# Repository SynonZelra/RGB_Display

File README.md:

RGB Display
===========	
During my work term at Lumotune I worked with developed LCD drivers and wanted to try a completely different type of display that I would be able to make on my own so I looked into making a RGB display. Just like the LED cube, multiplexing and persistence of vision were key techniques required. I used PWM drivers (TLC5940) to drive the specific values to the RGB LEDs in each column and shift registers (CD4094B) to switch between the rows. 
This is the first personal project dealing with complex IC so an online tutorial and base TLC5940 code from Kevin Darrah was used and expanded on: https://www.youtube.com/watch?v=FehBLNHMlfo 

This code was used instead of existing libraries to understand lower level programming and in depth use of TLC5940.
	
Updates:
--------
-	Original design was for 32 columns. This was reduced to 16 columns due to lack of RGB LEDs. The other sections have been updated to take this change into account.

Here is an image of the 16x16 RGB Display:  

Click below for a video of the display:  
<a href="https://youtu.be/2PrOFA3ZqBM">https://youtu.be/2PrOFA3ZqBM</a>

Materials:
----------
(Material list has been updated)
-	x256, 5mm RGB LED
    -	Common anode for PWM driver to sink current, see Figure 1
-	x3, PWM driver [TLC5940](http://www.ti.com/lit/ds/symlink/tlc5940.pdf)
    -	16 channels per chip
    -	12-bit PWM resolution
    -	6-bit dot correction resolution
    -	Current sink
    -	Daisy-chained
-	x2, shift register [CD4094B](http://www.ti.com/lit/ds/symlink/cd4094b.pdf)
    -	8 outputs per chip
    -	Daisy-chained
-	x16, p-channel MOSFET [ZVP4424A](http://www.diodes.com/datasheets/ZVP4424A.pdf) 
-	x5, 0.1uF ceramic capacitor, package 0805
-	x5, 1uF ceramic capacitor, package 0805
-	x2, 10uF tantalum capacitor
-	x1, 5V LDO regulator [LT1096CT](http://cds.linear.com/docs/en/datasheet/1086ffs.pdf)
-	x2, 1x6 female connector header
-	x1, 2.1mm power connector jack
-	x3, 28 position IC socket 
-	Soldering assembly (solder, iron, braid, etc.)
-	Breadboard and jumper wires

Design:
-------
-	LEDs were arranged in an array of 16x16 (256 LEDs, 48 pins per row) addressed by 3 PWM drivers (48 channels) and 2 shift registers (16 outputs)
-	Column data input to PWM drivers through SPI protocol, lighting an entire row at once and row is switched with shift register and new RGB data is sent through PWM driver
-	Shift register cant source enough current to light 16 LEDs so a p-channel MOSFET is used as a high side switch at each row to source required current
-	Base code from Kevin Darrah included:
    -	8-bit to 12-bit conversion for GS data transmission
    -	SPI protocol and timer interrupt setup 
-	Code was expanded on to include:
    -	Brightness and colour correction
    -	8-bit data resolution for easier storage and processing
    -	Shift register, data buffer and multiplexing
-	Schematic capture and PCB layout designed with CadSoft EAGLE

Figure 1: Common Anode RGB LED

Assembly:
---------
Prototype and assembly of RGB display can be seen from the images and videos below:  
  
Figure 2: Testing TLC5940 

Figure 3: 0000104_135116, Testing 2 row multiplexing with TLC5940 and CD4094B  

<a href="https://youtu.be/0XYK6YoSBJY">https://youtu.be/0XYK6YoSBJY</a>  
Video 1: TLCCycle2, Video of cycling through all the colours with TLC5940

<a href="https://youtu.be/0XYK6YoSBJY">https://youtu.be/0XYK6YoSBJY</a>  
Video 2: TLCShift, Video of shifting colours with TLC5940

Figure 4: PCB from SeeedStudio

Figure 5: Soldering the PCB

Figure 6: Testing and debugging the board (malfunctioning MOSFET) while soldering 

Figure 7: 16x16 RGB LED soldered!

Future:
-------
-	Update software to use TLC5940 and TLC5940Mux libraries
-	Import images with Python through serial port and show on RGB display

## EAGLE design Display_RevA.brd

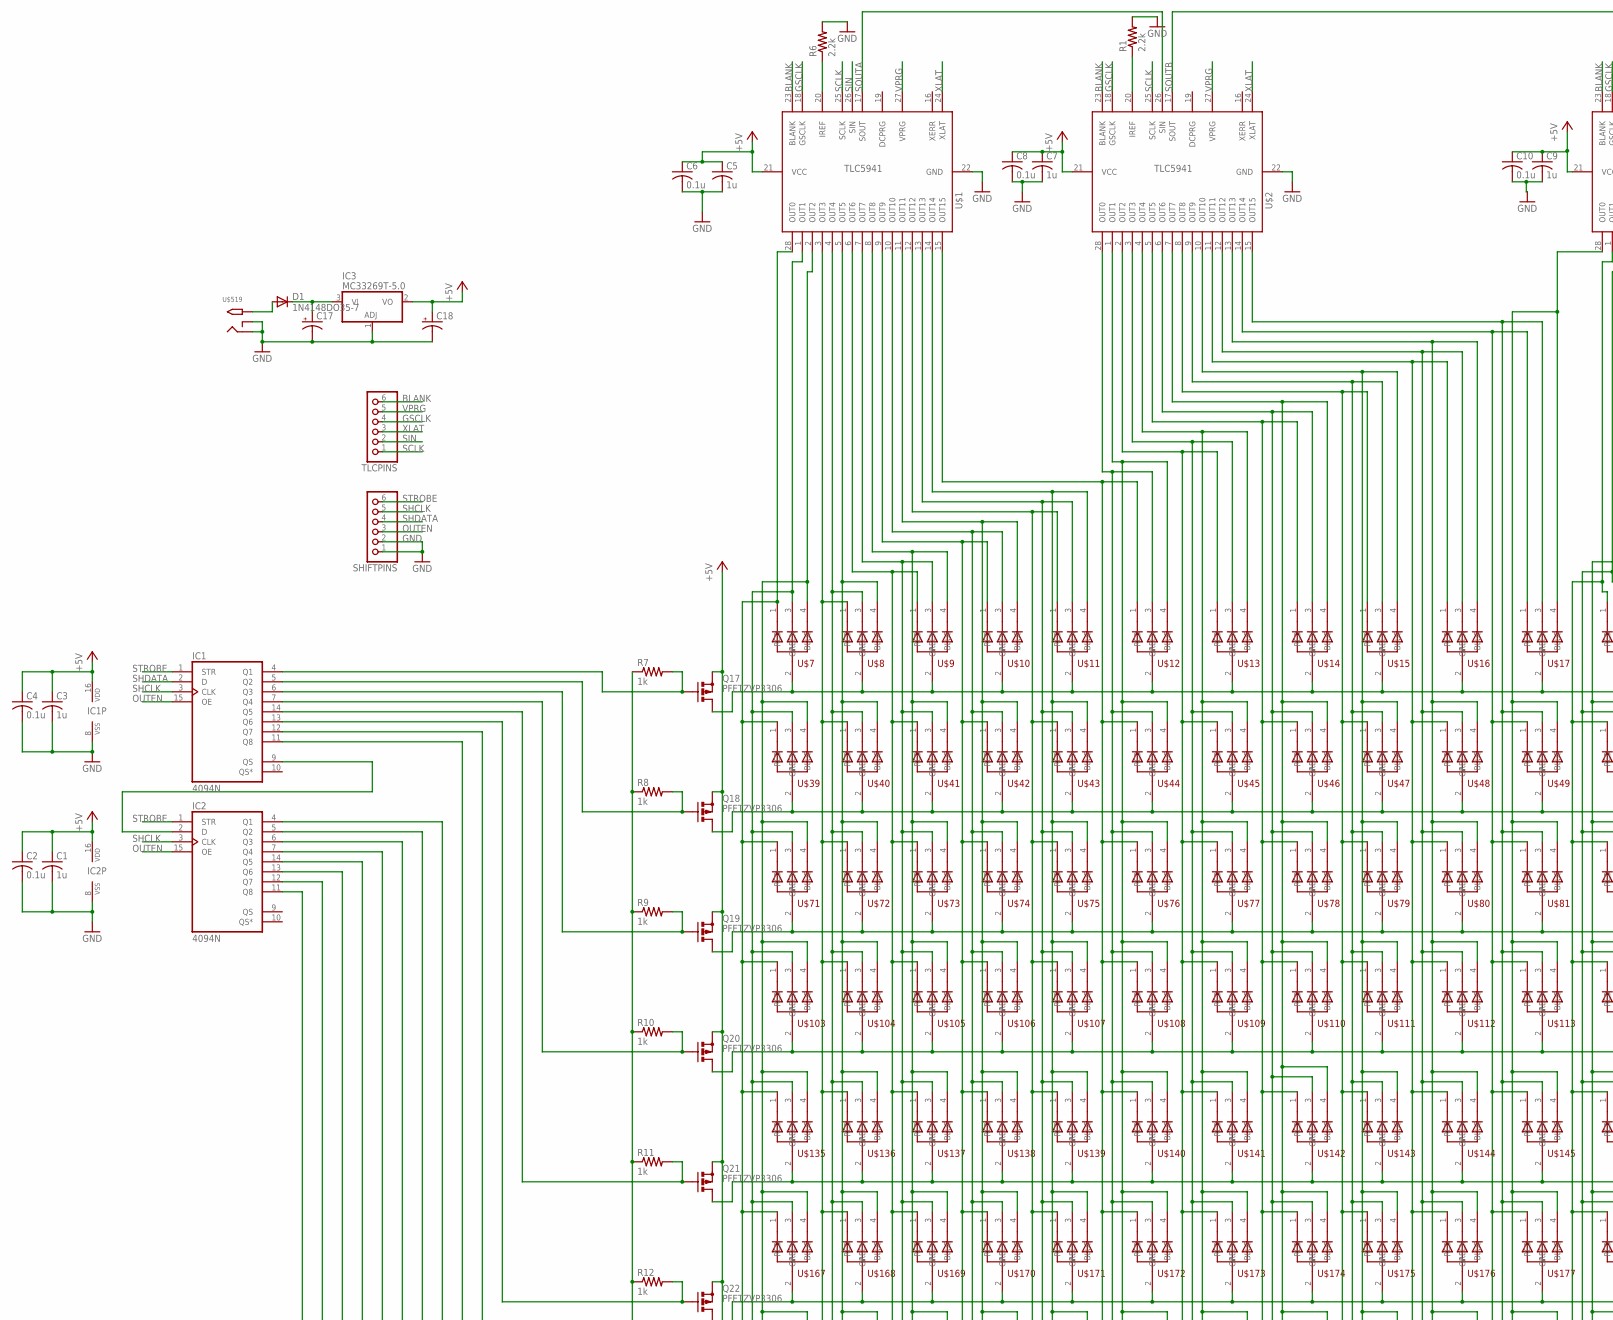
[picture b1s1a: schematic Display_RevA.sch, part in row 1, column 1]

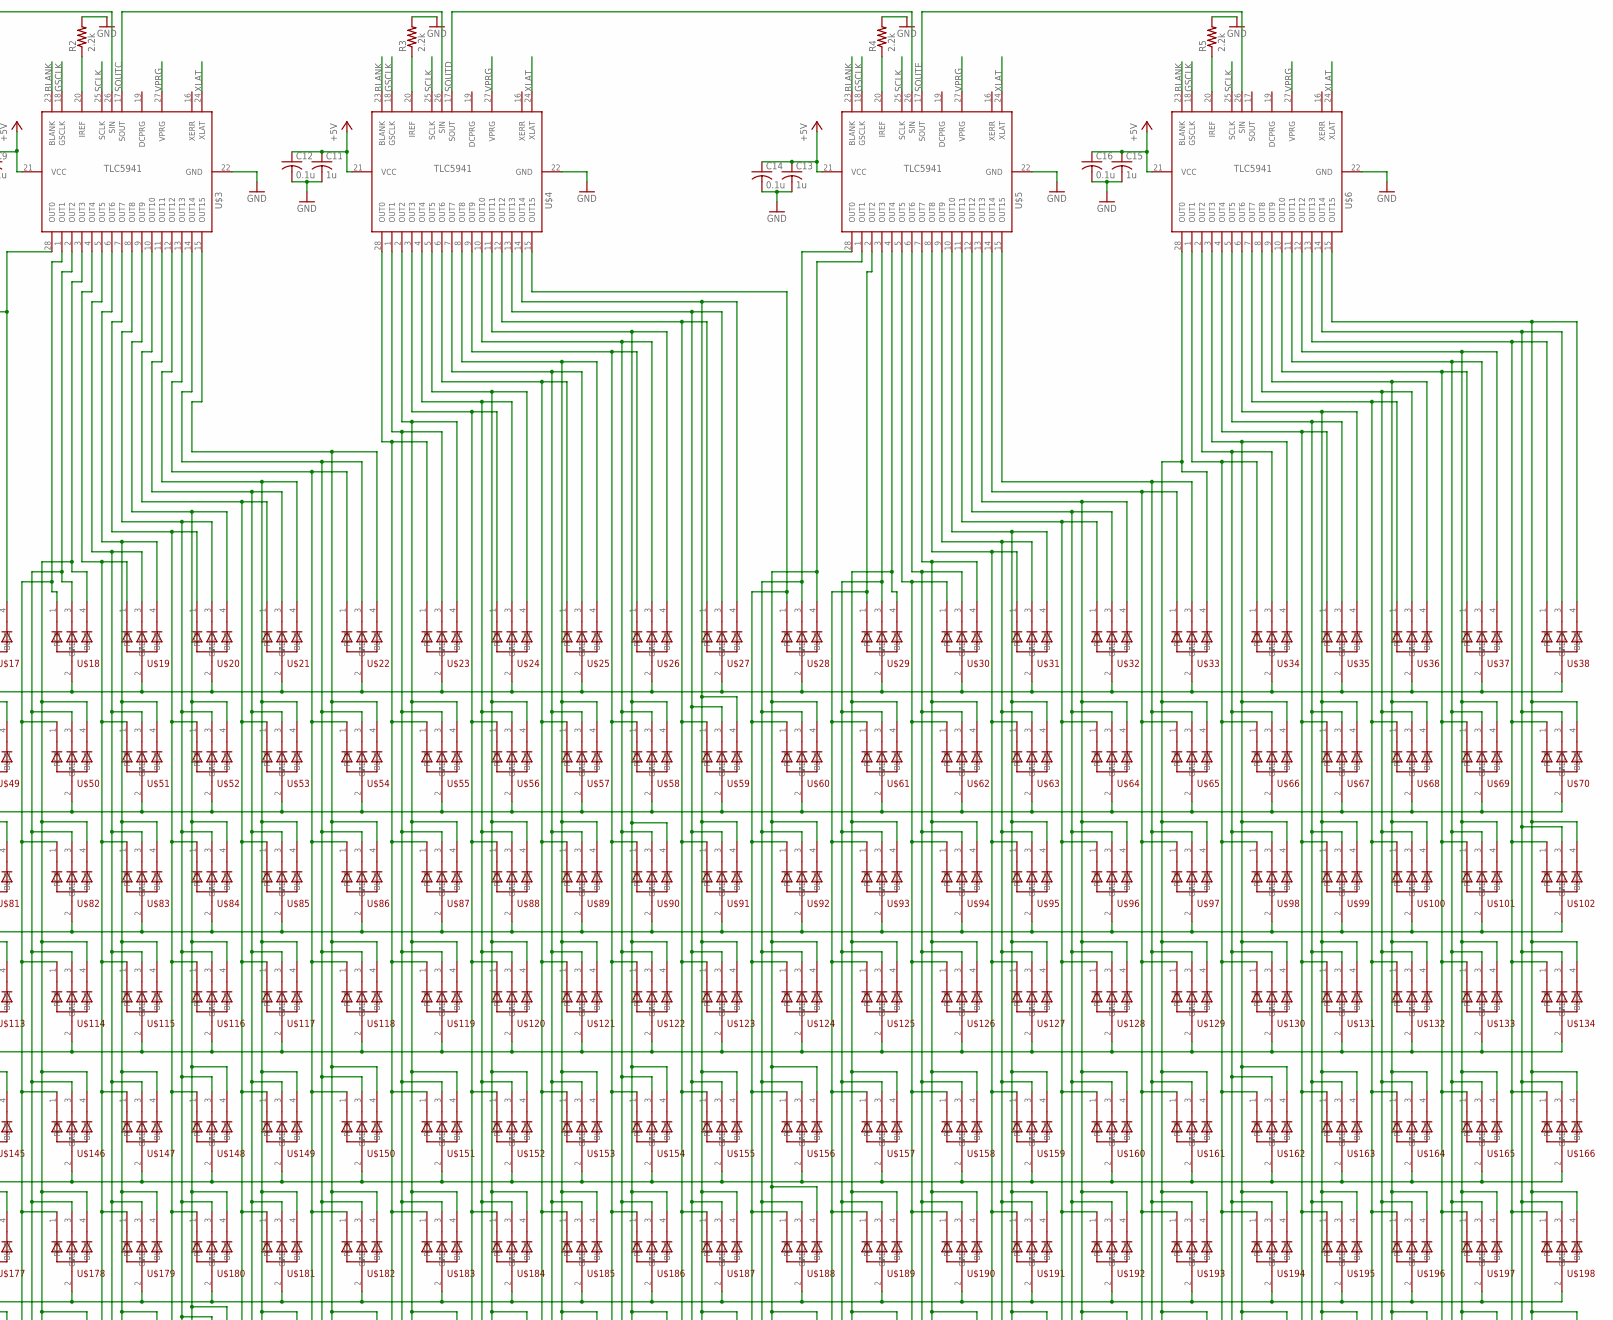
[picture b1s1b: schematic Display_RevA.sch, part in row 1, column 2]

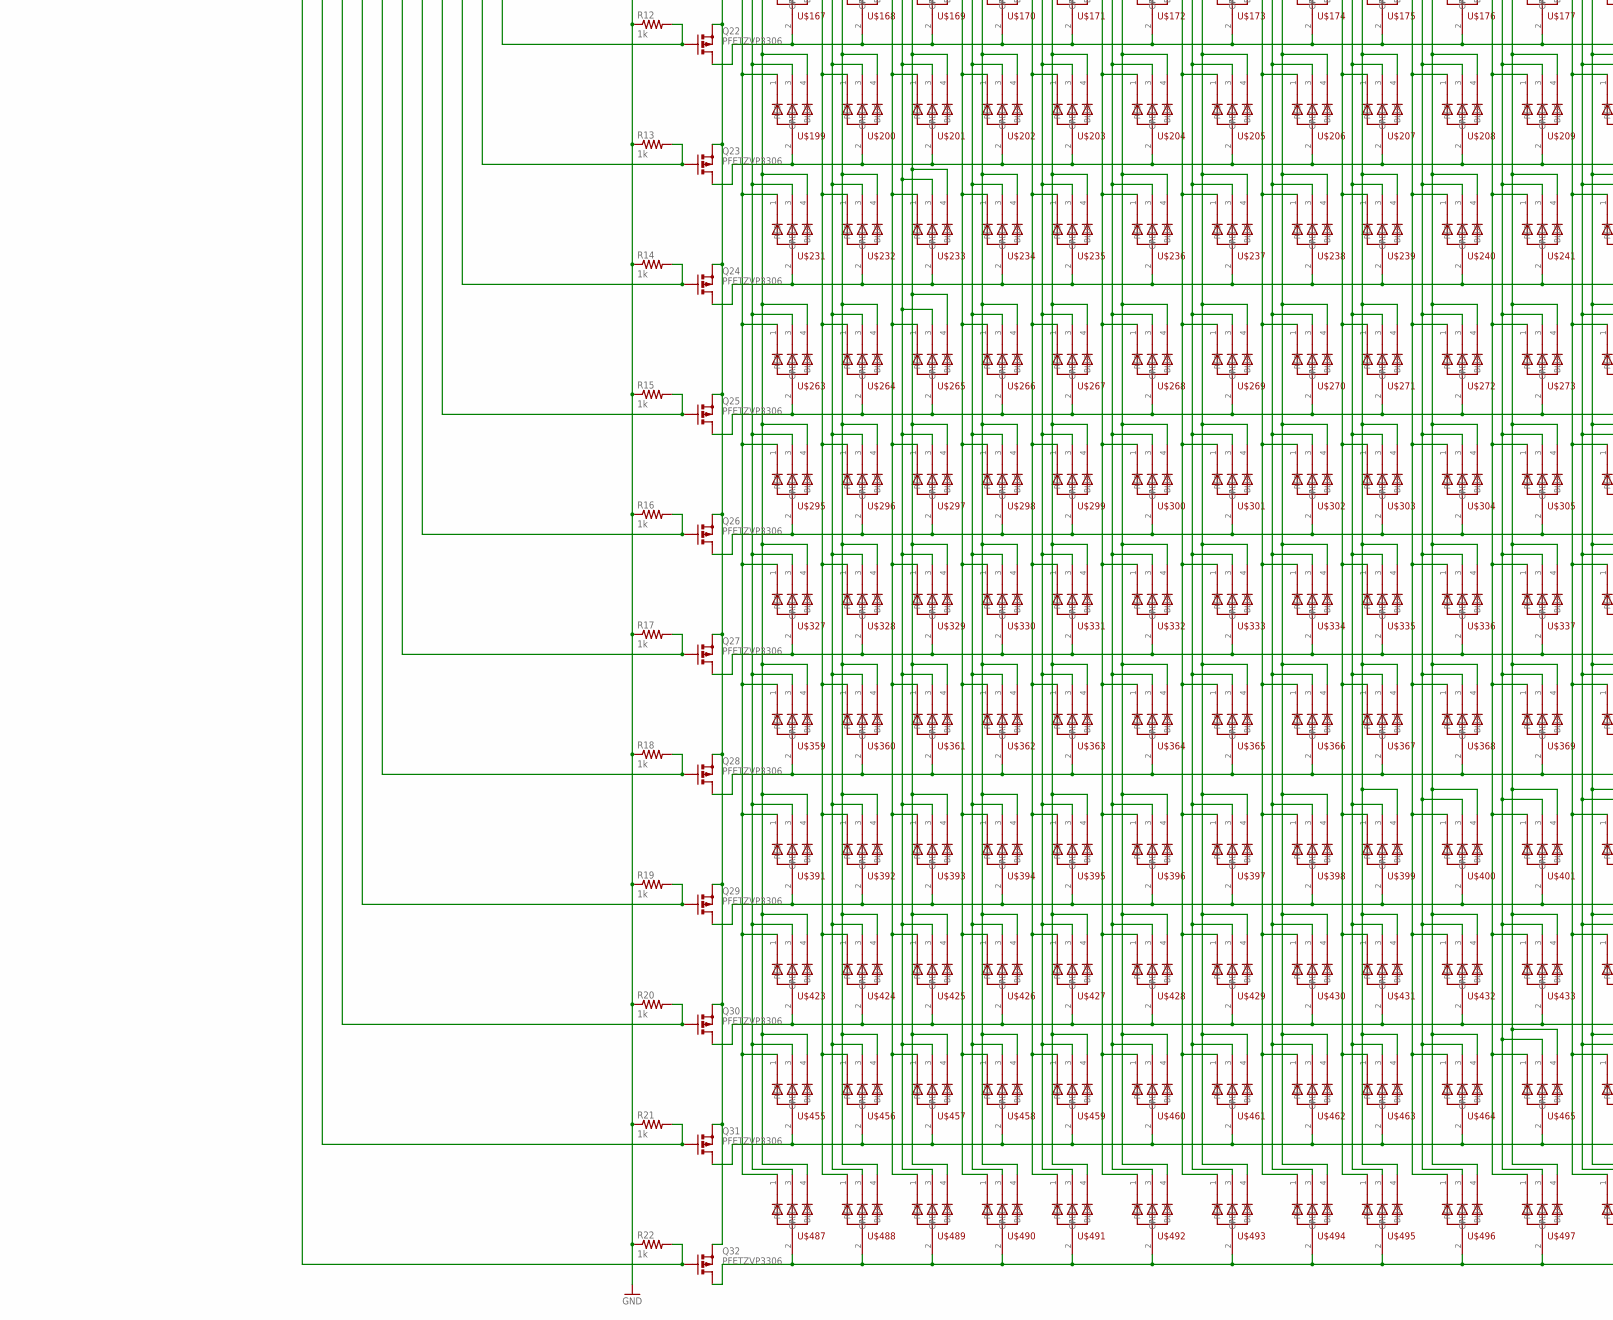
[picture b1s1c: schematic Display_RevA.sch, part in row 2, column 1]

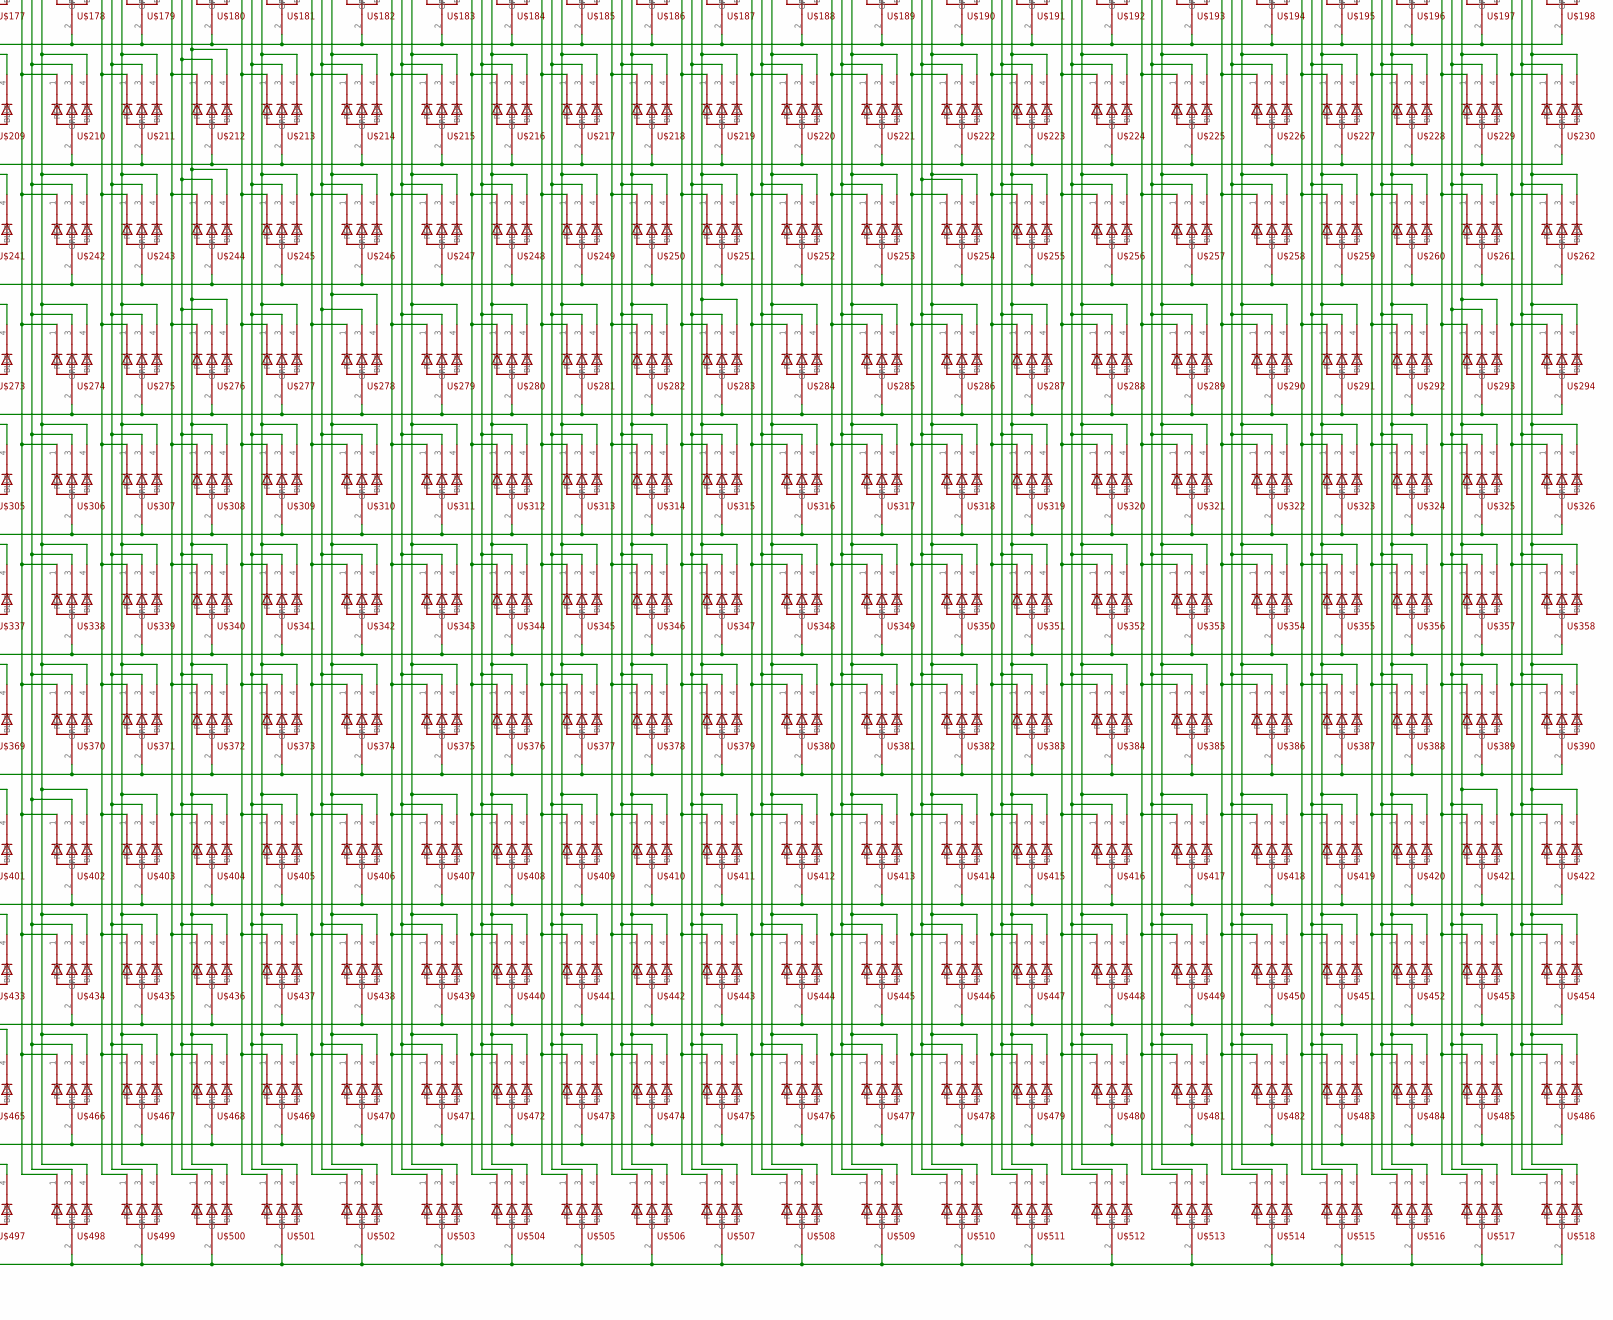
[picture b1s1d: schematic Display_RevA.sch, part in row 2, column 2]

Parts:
C1, C3, C5, C7, C9, C11, C13, C15: 1u; C0805
C2, C4, C6, C8, C10, C12, C14, C16: 0.1u; C0805
C17, C18: CPOL-USE2.5-5; E2,5-5
D1: 1N4148DO35-7; DO35-7
IC1, IC2: 4094N; DIL16
IC3: MC33269T-5.0; TO220V
Q17, Q18, Q19, Q20, Q21, Q22, Q23, Q24, Q25, Q26, Q27, Q28, Q29, Q30, Q31, Q32: PFETZVP3306; TO92-OVAL
R1, R2, R3, R4, R5, R6: 2.2k; R0805
R7, R8, R9, R10, R11, R12, R13, R14, R15, R16, R17, R18, R19, R20, R21, R22: 1k; R0805
SHIFTPINS: PINHD-1X6; 1X06
TLCPINS: PINHD-1X6; 1X06
U$1, U$2, U$3, U$4, U$5, U$6: TLC5940; DIL28-3
U$7, U$8, U$9, U$10, U$11, U$12, U$13, U$14, U$15, U$16, U$17, U$18, U$19, U$20, U$21, U$22, U$23, U$24, U$25, U$26, U$27, U$28, U$29, U$30, U$31, U$32, U$33, U$34, U$35, U$36, U$37, U$38, U$39, U$40, U$41, U$42, U$43, U$44, U$45, U$46, U$47, U$48, U$49, U$50, U$51, U$52, U$53, U$54, U$55, U$56, U$57, U$58, U$59, U$60, U$61, U$62, U$63, U$64, U$65, U$66, U$67, U$68, U$69, U$70, U$71, U$72, U$73, U$74, U$75, U$76, U$77, U$78, U$79, U$80, U$81, U$82, U$83, U$84, U$85, U$86, U$87, U$88, U$89, U$90, U$91, U$92, U$93, U$94, U$95, U$96, U$97, U$98, U$99, U$100, U$101, U$102, U$103, U$104, U$105, U$106, U$107, U$108, U$109, U$110, U$111, U$112, U$113, U$114, U$115, U$116, U$117, U$118, U$119, U$120, U$121, U$122, U$123, U$124, U$125, U$126, U$127, U$128, U$129, U$130, U$131, U$132, U$133, U$134, U$135, U$136, U$137, U$138, U$139, U$140, U$141, U$142, U$143, U$144, U$145, U$146, U$147, U$148, U$149, U$150, U$151, U$152, U$153, U$154, U$155, U$156, U$157, U$158, U$159, U$160, U$161, U$162, U$163, U$164, U$165, U$166, U$167, U$168, U$169, U$170, U$171, U$172, U$173, U$174, U$175, U$176, U$177, U$178, U$179, U$180, U$181, U$182, U$183, U$184, U$185, U$186, U$187, U$188, U$189, U$190, U$191, U$192, U$193, U$194, U$195, U$196, U$197, U$198, U$199, U$200, U$201, U$202, U$203, U$204, U$205, U$206, U$207, U$208, U$209, U$210, U$211, U$212, U$213, U$214, U$215, U$216, U$217, U$218, U$219, U$220, U$221, U$222, U$223, U$224, U$225, U$226, U$227, U$228, U$229, U$230, U$231, U$232, U$233, U$234, U$235, U$236, U$237, U$238, U$239, U$240, U$241, U$242, U$243, U$244, U$245, U$246, U$247, U$248, U$249, U$250, U$251, U$252, U$253, U$254, U$255, U$256, U$257, U$258, U$259, U$260, U$261, U$262, U$263, U$264, U$265, U$266, U$267, U$268, U$269, U$270, U$271, U$272, U$273, U$274, U$275, U$276, U$277, U$278, U$279, U$280, U$281, U$282, U$283, U$284, U$285, U$286, U$287, U$288, U$289, U$290, U$291, U$292, U$293, U$294, U$295, U$296, U$297, U$298, U$299, U$300, U$301, U$302, U$303, U$304, U$305, U$306, U$307, U$308, U$309, U$310, U$311, U$312, U$313, U$314, U$315, U$316, U$317, U$318, U$319, U$320, U$321, U$322, U$323, U$324, U$325, U$326, U$327, U$328, U$329, U$330, U$331, U$332, U$333, U$334, U$335, U$336, U$337, U$338, U$339, U$340, U$341, U$342, U$343, U$344, U$345, U$346, U$347, U$348, U$349, U$350, U$351, U$352, U$353, U$354, U$355, U$356, U$357, U$358, U$359, U$360, U$361, U$362, U$363, U$364, U$365, U$366, U$367, U$368, U$369, U$370, U$371, U$372, U$373, U$374, U$375, U$376, U$377, U$378, U$379, U$380, U$381, U$382, U$383, U$384, U$385, U$386, U$387, U$388, U$389, U$390, U$391, U$392, U$393, U$394, U$395, U$396, U$397, U$398, U$399, U$400, U$401, U$402, U$403, U$404, U$405, U$406, U$407, U$408, U$409, U$410, U$411, U$412, U$413, U$414, U$415, U$416, U$417, U$418, U$419, U$420, U$421, U$422, U$423, U$424, U$425, U$426, U$427, U$428, U$429, U$430, U$431, U$432, U$433, U$434, U$435, U$436, U$437, U$438, U$439, U$440, U$441, U$442, U$443, U$444, U$445, U$446, U$447, U$448, U$449, U$450, U$451, U$452, U$453, U$454, U$455, U$456, U$457, U$458, U$459, U$460, U$461, U$462, U$463, U$464, U$465, U$466, U$467, U$468, U$469, U$470, U$471, U$472, U$473, U$474, U$475, U$476, U$477, U$478, U$479, U$480, U$481, U$482, U$483, U$484, U$485, U$486, U$487, U$488, U$489, U$490, U$491, U$492, U$493, U$494, U$495, U$496, U$497, U$498, U$499, U$500, U$501, U$502, U$503, U$504, U$505, U$506, U$507, U$508, U$509, U$510, U$511, U$512, U$513, U$514, U$515, U$516, U$517, U$518: RGBLEDAN; LED5MMRGB
U$519: 2.1MMJACKTHM; PJ-102A

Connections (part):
+5V: C1.1, C2.1, C3.1, C4.1, C5.1, C6.1, C7.1, C8.1, C9.1, C10.1, C11.1, C12.1, C13.1, C14.1, C15.1, C16.1, C18.+, IC1.16 (VDD), IC2.16 (VDD), IC3.2 (VO), Q17.1 (S), Q18.1 (S), Q19.1 (S), Q20.1 (S), Q21.1 (S), Q22.1 (S), Q23.1 (S), Q24.1 (S), Q25.1 (S), Q26.1 (S), Q27.1 (S), Q28.1 (S), Q29.1 (S), Q30.1 (S), Q31.1 (S), Q32.1 (S), U$1.21 (VCC), U$2.21 (VCC), U$3.21 (VCC), U$4.21 (VCC), U$5.21 (VCC), U$6.21 (VCC)
BLANK: TLCPINS.6, U$1.23 (BLANK), U$2.23 (BLANK), U$3.23 (BLANK), U$4.23 (BLANK), U$5.23 (BLANK), U$6.23 (BLANK)
GND: C1.2, C2.2, C3.2, C4.2, C5.2, C6.2, C7.2, C8.2, C9.2, C10.2, C11.2, C12.2, C13.2, C14.2, C15.2, C16.2, C17.-, C18.-, IC1.8 (VSS), IC2.8 (VSS), IC3.1 (ADJ), R1.2, R2.2, R3.2, R4.2, R5.2, R6.2, R7.1, R8.1, R9.1, R10.1, R11.1, R12.1, R13.1, R14.1, R15.1, R16.1, R17.1, R18.1, R19.1, R20.1, R21.1, R22.1, SHIFTPINS.1, SHIFTPINS.2, U$1.22 (GND), U$2.22 (GND), U$3.22 (GND), U$4.22 (GND), U$5.22 (GND), U$6.22 (GND), U$519.RING, U$519.RING_SW
GSCLK: TLCPINS.4, U$1.18 (GSCLK), U$2.18 (GSCLK), U$3.18 (GSCLK), U$4.18 (GSCLK), U$5.18 (GSCLK), U$6.18 (GSCLK)
unnamed: IC1.5 (Q2), Q18.2 (G), R8.2
unnamed: Q18.3 (D), U$39.2 (V), U$40.2 (V), U$41.2 (V), U$42.2 (V), U$43.2 (V), U$44.2 (V), U$45.2 (V), U$46.2 (V), U$47.2 (V), U$48.2 (V), U$49.2 (V), U$50.2 (V), U$51.2 (V), U$52.2 (V), U$53.2 (V), U$54.2 (V), U$55.2 (V), U$56.2 (V), U$57.2 (V), U$58.2 (V), U$59.2 (V), U$60.2 (V), U$61.2 (V), U$62.2 (V), U$63.2 (V), U$64.2 (V), U$65.2 (V), U$66.2 (V), U$67.2 (V), U$68.2 (V), U$69.2 (V), U$70.2 (V)
unnamed: IC1.6 (Q3), Q19.2 (G), R9.2
unnamed: Q19.3 (D), U$71.2 (V), U$72.2 (V), U$73.2 (V), U$74.2 (V), U$75.2 (V), U$76.2 (V), U$77.2 (V), U$78.2 (V), U$79.2 (V), U$80.2 (V), U$81.2 (V), U$82.2 (V), U$83.2 (V), U$84.2 (V), U$85.2 (V), U$86.2 (V), U$87.2 (V), U$88.2 (V), U$89.2 (V), U$90.2 (V), U$91.2 (V), U$92.2 (V), U$93.2 (V), U$94.2 (V), U$95.2 (V), U$96.2 (V), U$97.2 (V), U$98.2 (V), U$99.2 (V), U$100.2 (V), U$101.2 (V), U$102.2 (V)
unnamed: IC1.7 (Q4), Q20.2 (G), R10.2
unnamed: Q20.3 (D), U$103.2 (V), U$104.2 (V), U$105.2 (V), U$106.2 (V), U$107.2 (V), U$108.2 (V), U$109.2 (V), U$110.2 (V), U$111.2 (V), U$112.2 (V), U$113.2 (V), U$114.2 (V), U$115.2 (V), U$116.2 (V), U$117.2 (V), U$118.2 (V), U$119.2 (V), U$120.2 (V), U$121.2 (V), U$122.2 (V), U$123.2 (V), U$124.2 (V), U$125.2 (V), U$126.2 (V), U$127.2 (V), U$128.2 (V), U$129.2 (V), U$130.2 (V), U$131.2 (V), U$132.2 (V), U$133.2 (V), U$134.2 (V)
unnamed: IC1.14 (Q5), Q21.2 (G), R11.2
unnamed: Q21.3 (D), U$135.2 (V), U$136.2 (V), U$137.2 (V), U$138.2 (V), U$139.2 (V), U$140.2 (V), U$141.2 (V), U$142.2 (V), U$143.2 (V), U$144.2 (V), U$145.2 (V), U$146.2 (V), U$147.2 (V), U$148.2 (V), U$149.2 (V), U$150.2 (V), U$151.2 (V), U$152.2 (V), U$153.2 (V), U$154.2 (V), U$155.2 (V), U$156.2 (V), U$157.2 (V), U$158.2 (V), U$159.2 (V), U$160.2 (V), U$161.2 (V), U$162.2 (V), U$163.2 (V), U$164.2 (V), U$165.2 (V), U$166.2 (V)
unnamed: IC1.13 (Q6), Q22.2 (G), R12.2
unnamed: Q22.3 (D), U$167.2 (V), U$168.2 (V), U$169.2 (V), U$170.2 (V), U$171.2 (V), U$172.2 (V), U$173.2 (V), U$174.2 (V), U$175.2 (V), U$176.2 (V), U$177.2 (V), U$178.2 (V), U$179.2 (V), U$180.2 (V), U$181.2 (V), U$182.2 (V), U$183.2 (V), U$184.2 (V), U$185.2 (V), U$186.2 (V), U$187.2 (V), U$188.2 (V), U$189.2 (V), U$190.2 (V), U$191.2 (V), U$192.2 (V), U$193.2 (V), U$194.2 (V), U$195.2 (V), U$196.2 (V), U$197.2 (V), U$198.2 (V)
unnamed: IC1.12 (Q7), Q23.2 (G), R13.2
unnamed: Q23.3 (D), U$199.2 (V), U$200.2 (V), U$201.2 (V), U$202.2 (V), U$203.2 (V), U$204.2 (V), U$205.2 (V), U$206.2 (V), U$207.2 (V), U$208.2 (V), U$209.2 (V), U$210.2 (V), U$211.2 (V), U$212.2 (V), U$213.2 (V), U$214.2 (V), U$215.2 (V), U$216.2 (V), U$217.2 (V), U$218.2 (V), U$219.2 (V), U$220.2 (V), U$221.2 (V), U$222.2 (V), U$223.2 (V), U$224.2 (V), U$225.2 (V), U$226.2 (V), U$227.2 (V), U$228.2 (V), U$229.2 (V), U$230.2 (V)
unnamed: IC1.11 (Q8), Q24.2 (G), R14.2
unnamed: Q24.3 (D), U$231.2 (V), U$232.2 (V), U$233.2 (V), U$234.2 (V), U$235.2 (V), U$236.2 (V), U$237.2 (V), U$238.2 (V), U$239.2 (V), U$240.2 (V), U$241.2 (V), U$242.2 (V), U$243.2 (V), U$244.2 (V), U$245.2 (V), U$246.2 (V), U$247.2 (V), U$248.2 (V), U$249.2 (V), U$250.2 (V), U$251.2 (V), U$252.2 (V), U$253.2 (V), U$254.2 (V), U$255.2 (V), U$256.2 (V), U$257.2 (V), U$258.2 (V), U$259.2 (V), U$260.2 (V), U$261.2 (V), U$262.2 (V)
unnamed: IC2.4 (Q1), Q25.2 (G), R15.2
unnamed: IC1.4 (Q1), Q17.2 (G), R7.2
unnamed: Q17.3 (D), U$7.2 (V), U$8.2 (V), U$9.2 (V), U$10.2 (V), U$11.2 (V), U$12.2 (V), U$13.2 (V), U$14.2 (V), U$15.2 (V), U$16.2 (V), U$17.2 (V), U$18.2 (V), U$19.2 (V), U$20.2 (V), U$21.2 (V), U$22.2 (V), U$23.2 (V), U$24.2 (V), U$25.2 (V), U$26.2 (V), U$27.2 (V), U$28.2 (V), U$29.2 (V), U$30.2 (V), U$31.2 (V), U$32.2 (V), U$33.2 (V), U$34.2 (V), U$35.2 (V), U$36.2 (V), U$37.2 (V), U$38.2 (V)
unnamed: Q25.3 (D), U$263.2 (V), U$264.2 (V), U$265.2 (V), U$266.2 (V), U$267.2 (V), U$268.2 (V), U$269.2 (V), U$270.2 (V), U$271.2 (V), U$272.2 (V), U$273.2 (V), U$274.2 (V), U$275.2 (V), U$276.2 (V), U$277.2 (V), U$278.2 (V), U$279.2 (V), U$280.2 (V), U$281.2 (V), U$282.2 (V), U$283.2 (V), U$284.2 (V), U$285.2 (V), U$286.2 (V), U$287.2 (V), U$288.2 (V), U$289.2 (V), U$290.2 (V), U$291.2 (V), U$292.2 (V), U$293.2 (V), U$294.2 (V)
unnamed: IC2.5 (Q2), Q26.2 (G), R16.2
unnamed: Q26.3 (D), U$295.2 (V), U$296.2 (V), U$297.2 (V), U$298.2 (V), U$299.2 (V), U$300.2 (V), U$301.2 (V), U$302.2 (V), U$303.2 (V), U$304.2 (V), U$305.2 (V), U$306.2 (V), U$307.2 (V), U$308.2 (V), U$309.2 (V), U$310.2 (V), U$311.2 (V), U$312.2 (V), U$313.2 (V), U$314.2 (V), U$315.2 (V), U$316.2 (V), U$317.2 (V), U$318.2 (V), U$319.2 (V), U$320.2 (V), U$321.2 (V), U$322.2 (V), U$323.2 (V), U$324.2 (V), U$325.2 (V), U$326.2 (V)
unnamed: IC2.6 (Q3), Q27.2 (G), R17.2
unnamed: Q27.3 (D), U$327.2 (V), U$328.2 (V), U$329.2 (V), U$330.2 (V), U$331.2 (V), U$332.2 (V), U$333.2 (V), U$334.2 (V), U$335.2 (V), U$336.2 (V), U$337.2 (V), U$338.2 (V), U$339.2 (V), U$340.2 (V), U$341.2 (V), U$342.2 (V), U$343.2 (V), U$344.2 (V), U$345.2 (V), U$346.2 (V), U$347.2 (V), U$348.2 (V), U$349.2 (V), U$350.2 (V), U$351.2 (V), U$352.2 (V), U$353.2 (V), U$354.2 (V), U$355.2 (V), U$356.2 (V), U$357.2 (V), U$358.2 (V)
unnamed: IC2.7 (Q4), Q28.2 (G), R18.2
unnamed: Q28.3 (D), U$359.2 (V), U$360.2 (V), U$361.2 (V), U$362.2 (V), U$363.2 (V), U$364.2 (V), U$365.2 (V), U$366.2 (V), U$367.2 (V), U$368.2 (V), U$369.2 (V), U$370.2 (V), U$371.2 (V), U$372.2 (V), U$373.2 (V), U$374.2 (V), U$375.2 (V), U$376.2 (V), U$377.2 (V), U$378.2 (V), U$379.2 (V), U$380.2 (V), U$381.2 (V), U$382.2 (V), U$383.2 (V), U$384.2 (V), U$385.2 (V), U$386.2 (V), U$387.2 (V), U$388.2 (V), U$389.2 (V), U$390.2 (V)
unnamed: IC2.14 (Q5), Q29.2 (G), R19.2
unnamed: Q29.3 (D), U$391.2 (V), U$392.2 (V), U$393.2 (V), U$394.2 (V), U$395.2 (V), U$396.2 (V), U$397.2 (V), U$398.2 (V), U$399.2 (V), U$400.2 (V), U$401.2 (V), U$402.2 (V), U$403.2 (V), U$404.2 (V), U$405.2 (V), U$406.2 (V), U$407.2 (V), U$408.2 (V), U$409.2 (V), U$410.2 (V), U$411.2 (V), U$412.2 (V), U$413.2 (V), U$414.2 (V), U$415.2 (V), U$416.2 (V), U$417.2 (V), U$418.2 (V), U$419.2 (V), U$420.2 (V), U$421.2 (V), U$422.2 (V)
unnamed: IC2.13 (Q6), Q30.2 (G), R20.2
unnamed: Q30.3 (D), U$423.2 (V), U$424.2 (V), U$425.2 (V), U$426.2 (V), U$427.2 (V), U$428.2 (V), U$429.2 (V), U$430.2 (V), U$431.2 (V), U$432.2 (V), U$433.2 (V), U$434.2 (V), U$435.2 (V), U$436.2 (V), U$437.2 (V), U$438.2 (V), U$439.2 (V), U$440.2 (V), U$441.2 (V), U$442.2 (V), U$443.2 (V), U$444.2 (V), U$445.2 (V), U$446.2 (V), U$447.2 (V), U$448.2 (V), U$449.2 (V), U$450.2 (V), U$451.2 (V), U$452.2 (V), U$453.2 (V), U$454.2 (V)
unnamed: IC2.12 (Q7), Q31.2 (G), R21.2
unnamed: Q31.3 (D), U$455.2 (V), U$456.2 (V), U$457.2 (V), U$458.2 (V), U$459.2 (V), U$460.2 (V), U$461.2 (V), U$462.2 (V), U$463.2 (V), U$464.2 (V), U$465.2 (V), U$466.2 (V), U$467.2 (V), U$468.2 (V), U$469.2 (V), U$470.2 (V), U$471.2 (V), U$472.2 (V), U$473.2 (V), U$474.2 (V), U$475.2 (V), U$476.2 (V), U$477.2 (V), U$478.2 (V), U$479.2 (V), U$480.2 (V), U$481.2 (V), U$482.2 (V), U$483.2 (V), U$484.2 (V), U$485.2 (V), U$486.2 (V)
unnamed: IC2.11 (Q8), Q32.2 (G), R22.2
unnamed: Q32.3 (D), U$487.2 (V), U$488.2 (V), U$489.2 (V), U$490.2 (V), U$491.2 (V), U$492.2 (V), U$493.2 (V), U$494.2 (V), U$495.2 (V), U$496.2 (V), U$497.2 (V), U$498.2 (V), U$499.2 (V), U$500.2 (V), U$501.2 (V), U$502.2 (V), U$503.2 (V), U$504.2 (V), U$505.2 (V), U$506.2 (V), U$507.2 (V), U$508.2 (V), U$509.2 (V), U$510.2 (V), U$511.2 (V), U$512.2 (V), U$513.2 (V), U$514.2 (V), U$515.2 (V), U$516.2 (V), U$517.2 (V), U$518.2 (V)
unnamed: U$1.28 (OUT0), U$7.1 (RED), U$39.1 (RED), U$71.1 (RED), U$103.1 (RED), U$135.1 (RED), U$167.1 (RED), U$199.1 (RED), U$231.1 (RED), U$263.1 (RED), U$295.1 (RED), U$327.1 (RED), U$359.1 (RED), U$391.1 (RED), U$423.1 (RED), U$455.1 (RED), U$487.1 (RED)
unnamed: U$1.1 (OUT1), U$7.3 (GREEN), U$39.3 (GREEN), U$71.3 (GREEN), U$103.3 (GREEN), U$135.3 (GREEN), U$167.3 (GREEN), U$199.3 (GREEN), U$231.3 (GREEN), U$263.3 (GREEN), U$295.3 (GREEN), U$327.3 (GREEN), U$359.3 (GREEN), U$391.3 (GREEN), U$423.3 (GREEN), U$455.3 (GREEN), U$487.3 (GREEN)
unnamed: U$1.2 (OUT2), U$7.4 (BLUE), U$39.4 (BLUE), U$71.4 (BLUE), U$103.4 (BLUE), U$135.4 (BLUE), U$167.4 (BLUE), U$199.4 (BLUE), U$231.4 (BLUE), U$263.4 (BLUE), U$295.4 (BLUE), U$327.4 (BLUE), U$359.4 (BLUE), U$391.4 (BLUE), U$423.4 (BLUE), U$455.4 (BLUE), U$487.4 (BLUE)
unnamed: U$1.3 (OUT3), U$8.1 (RED), U$40.1 (RED), U$72.1 (RED), U$104.1 (RED), U$136.1 (RED), U$168.1 (RED), U$200.1 (RED), U$232.1 (RED), U$264.1 (RED), U$296.1 (RED), U$328.1 (RED), U$360.1 (RED), U$392.1 (RED), U$424.1 (RED), U$456.1 (RED), U$488.1 (RED)
unnamed: IC1.9 (QS), IC2.2 (D)
unnamed: U$1.4 (OUT4), U$8.3 (GREEN), U$40.3 (GREEN), U$72.3 (GREEN), U$104.3 (GREEN), U$136.3 (GREEN), U$168.3 (GREEN), U$200.3 (GREEN), U$232.3 (GREEN), U$264.3 (GREEN), U$296.3 (GREEN), U$328.3 (GREEN), U$360.3 (GREEN), U$392.3 (GREEN), U$424.3 (GREEN), U$456.3 (GREEN), U$488.3 (GREEN)
unnamed: U$1.5 (OUT5), U$8.4 (BLUE), U$40.4 (BLUE), U$72.4 (BLUE), U$104.4 (BLUE), U$136.4 (BLUE), U$168.4 (BLUE), U$200.4 (BLUE), U$232.4 (BLUE), U$264.4 (BLUE), U$296.4 (BLUE), U$328.4 (BLUE), U$360.4 (BLUE), U$392.4 (BLUE), U$424.4 (BLUE), U$456.4 (BLUE), U$488.4 (BLUE)
unnamed: U$1.6 (OUT6), U$9.1 (RED), U$41.1 (RED), U$73.1 (RED), U$105.1 (RED), U$137.1 (RED), U$169.1 (RED), U$201.1 (RED), U$233.1 (RED), U$265.1 (RED), U$297.1 (RED), U$329.1 (RED), U$361.1 (RED), U$393.1 (RED), U$425.1 (RED), U$457.1 (RED), U$489.1 (RED)
unnamed: U$1.7 (OUT7), U$9.3 (GREEN), U$41.3 (GREEN), U$73.3 (GREEN), U$105.3 (GREEN), U$137.3 (GREEN), U$169.3 (GREEN), U$201.3 (GREEN), U$233.3 (GREEN), U$265.3 (GREEN), U$297.3 (GREEN), U$329.3 (GREEN), U$361.3 (GREEN), U$393.3 (GREEN), U$425.3 (GREEN), U$457.3 (GREEN), U$489.3 (GREEN)
unnamed: U$1.8 (OUT8), U$9.4 (BLUE), U$41.4 (BLUE), U$73.4 (BLUE), U$105.4 (BLUE), U$137.4 (BLUE), U$169.4 (BLUE), U$201.4 (BLUE), U$233.4 (BLUE), U$265.4 (BLUE), U$297.4 (BLUE), U$329.4 (BLUE), U$361.4 (BLUE), U$393.4 (BLUE), U$425.4 (BLUE), U$457.4 (BLUE), U$489.4 (BLUE)
unnamed: U$1.9 (OUT9), U$10.1 (RED), U$42.1 (RED), U$74.1 (RED), U$106.1 (RED), U$138.1 (RED), U$170.1 (RED), U$202.1 (RED), U$234.1 (RED), U$266.1 (RED), U$298.1 (RED), U$330.1 (RED), U$362.1 (RED), U$394.1 (RED), U$426.1 (RED), U$458.1 (RED), U$490.1 (RED)
unnamed: U$1.10 (OUT10), U$10.3 (GREEN), U$42.3 (GREEN), U$74.3 (GREEN), U$106.3 (GREEN), U$138.3 (GREEN), U$170.3 (GREEN), U$202.3 (GREEN), U$234.3 (GREEN), U$266.3 (GREEN), U$298.3 (GREEN), U$330.3 (GREEN), U$362.3 (GREEN), U$394.3 (GREEN), U$426.3 (GREEN), U$458.3 (GREEN), U$490.3 (GREEN)
unnamed: U$1.11 (OUT11), U$10.4 (BLUE), U$42.4 (BLUE), U$74.4 (BLUE), U$106.4 (BLUE), U$138.4 (BLUE), U$170.4 (BLUE), U$202.4 (BLUE), U$234.4 (BLUE), U$266.4 (BLUE), U$298.4 (BLUE), U$330.4 (BLUE), U$362.4 (BLUE), U$394.4 (BLUE), U$426.4 (BLUE), U$458.4 (BLUE), U$490.4 (BLUE)
unnamed: U$1.12 (OUT12), U$11.1 (RED), U$43.1 (RED), U$75.1 (RED), U$107.1 (RED), U$139.1 (RED), U$171.1 (RED), U$203.1 (RED), U$235.1 (RED), U$267.1 (RED), U$299.1 (RED), U$331.1 (RED), U$363.1 (RED), U$395.1 (RED), U$427.1 (RED), U$459.1 (RED), U$491.1 (RED)
unnamed: U$1.13 (OUT13), U$11.3 (GREEN), U$43.3 (GREEN), U$75.3 (GREEN), U$107.3 (GREEN), U$139.3 (GREEN), U$171.3 (GREEN), U$203.3 (GREEN), U$235.3 (GREEN), U$267.3 (GREEN), U$299.3 (GREEN), U$331.3 (GREEN), U$363.3 (GREEN), U$395.3 (GREEN), U$427.3 (GREEN), U$459.3 (GREEN), U$491.3 (GREEN)
unnamed: U$1.14 (OUT14), U$11.4 (BLUE), U$43.4 (BLUE), U$75.4 (BLUE), U$107.4 (BLUE), U$139.4 (BLUE), U$171.4 (BLUE), U$203.4 (BLUE), U$235.4 (BLUE), U$267.4 (BLUE), U$299.4 (BLUE), U$331.4 (BLUE), U$363.4 (BLUE), U$395.4 (BLUE), U$427.4 (BLUE), U$459.4 (BLUE), U$491.4 (BLUE)
unnamed: U$1.15 (OUT15), U$12.1 (RED), U$44.1 (RED), U$76.1 (RED), U$108.1 (RED), U$140.1 (RED), U$172.1 (RED), U$204.1 (RED), U$236.1 (RED), U$268.1 (RED), U$300.1 (RED), U$332.1 (RED), U$364.1 (RED), U$396.1 (RED), U$428.1 (RED), U$460.1 (RED), U$492.1 (RED)
unnamed: U$2.28 (OUT0), U$12.3 (GREEN), U$44.3 (GREEN), U$76.3 (GREEN), U$108.3 (GREEN), U$140.3 (GREEN), U$172.3 (GREEN), U$204.3 (GREEN), U$236.3 (GREEN), U$268.3 (GREEN), U$300.3 (GREEN), U$332.3 (GREEN), U$364.3 (GREEN), U$396.3 (GREEN), U$428.3 (GREEN), U$460.3 (GREEN), U$492.3 (GREEN)
unnamed: U$2.1 (OUT1), U$12.4 (BLUE), U$44.4 (BLUE), U$76.4 (BLUE), U$108.4 (BLUE), U$140.4 (BLUE), U$172.4 (BLUE), U$204.4 (BLUE), U$236.4 (BLUE), U$268.4 (BLUE), U$300.4 (BLUE), U$332.4 (BLUE), U$364.4 (BLUE), U$396.4 (BLUE), U$428.4 (BLUE), U$460.4 (BLUE), U$492.4 (BLUE)
unnamed: U$2.2 (OUT2), U$13.1 (RED), U$45.1 (RED), U$77.1 (RED), U$109.1 (RED), U$141.1 (RED), U$173.1 (RED), U$205.1 (RED), U$237.1 (RED), U$269.1 (RED), U$301.1 (RED), U$333.1 (RED), U$365.1 (RED), U$397.1 (RED), U$429.1 (RED), U$461.1 (RED), U$493.1 (RED)
unnamed: U$2.3 (OUT3), U$13.3 (GREEN), U$45.3 (GREEN), U$77.3 (GREEN), U$109.3 (GREEN), U$141.3 (GREEN), U$173.3 (GREEN), U$205.3 (GREEN), U$237.3 (GREEN), U$269.3 (GREEN), U$301.3 (GREEN), U$333.3 (GREEN), U$365.3 (GREEN), U$397.3 (GREEN), U$429.3 (GREEN), U$461.3 (GREEN), U$493.3 (GREEN)
unnamed: U$2.4 (OUT4), U$13.4 (BLUE), U$45.4 (BLUE), U$77.4 (BLUE), U$109.4 (BLUE), U$141.4 (BLUE), U$173.4 (BLUE), U$205.4 (BLUE), U$237.4 (BLUE), U$269.4 (BLUE), U$301.4 (BLUE), U$333.4 (BLUE), U$365.4 (BLUE), U$397.4 (BLUE), U$429.4 (BLUE), U$461.4 (BLUE), U$493.4 (BLUE)
unnamed: U$2.5 (OUT5), U$14.1 (RED), U$46.1 (RED), U$78.1 (RED), U$110.1 (RED), U$142.1 (RED), U$174.1 (RED), U$206.1 (RED), U$238.1 (RED), U$270.1 (RED), U$302.1 (RED), U$334.1 (RED), U$366.1 (RED), U$398.1 (RED), U$430.1 (RED), U$462.1 (RED), U$494.1 (RED)
unnamed: U$2.6 (OUT6), U$14.3 (GREEN), U$46.3 (GREEN), U$78.3 (GREEN), U$110.3 (GREEN), U$142.3 (GREEN), U$174.3 (GREEN), U$206.3 (GREEN), U$238.3 (GREEN), U$270.3 (GREEN), U$302.3 (GREEN), U$334.3 (GREEN), U$366.3 (GREEN), U$398.3 (GREEN), U$430.3 (GREEN), U$462.3 (GREEN), U$494.3 (GREEN)
unnamed: U$2.7 (OUT7), U$14.4 (BLUE), U$46.4 (BLUE), U$78.4 (BLUE), U$110.4 (BLUE), U$142.4 (BLUE), U$174.4 (BLUE), U$206.4 (BLUE), U$238.4 (BLUE), U$270.4 (BLUE), U$302.4 (BLUE), U$334.4 (BLUE), U$366.4 (BLUE), U$398.4 (BLUE), U$430.4 (BLUE), U$462.4 (BLUE), U$494.4 (BLUE)
unnamed: U$2.8 (OUT8), U$15.1 (RED), U$47.1 (RED), U$79.1 (RED), U$111.1 (RED), U$143.1 (RED), U$175.1 (RED), U$207.1 (RED), U$239.1 (RED), U$271.1 (RED), U$303.1 (RED), U$335.1 (RED), U$367.1 (RED), U$399.1 (RED), U$431.1 (RED), U$463.1 (RED), U$495.1 (RED)
unnamed: U$2.9 (OUT9), U$15.3 (GREEN), U$47.3 (GREEN), U$79.3 (GREEN), U$111.3 (GREEN), U$143.3 (GREEN), U$175.3 (GREEN), U$207.3 (GREEN), U$239.3 (GREEN), U$271.3 (GREEN), U$303.3 (GREEN), U$335.3 (GREEN), U$367.3 (GREEN), U$399.3 (GREEN), U$431.3 (GREEN), U$463.3 (GREEN), U$495.3 (GREEN)
unnamed: U$2.10 (OUT10), U$15.4 (BLUE), U$47.4 (BLUE), U$79.4 (BLUE), U$111.4 (BLUE), U$143.4 (BLUE), U$175.4 (BLUE), U$207.4 (BLUE), U$239.4 (BLUE), U$271.4 (BLUE), U$303.4 (BLUE), U$335.4 (BLUE), U$367.4 (BLUE), U$399.4 (BLUE), U$431.4 (BLUE), U$463.4 (BLUE), U$495.4 (BLUE)
unnamed: U$2.11 (OUT11), U$16.1 (RED), U$48.1 (RED), U$80.1 (RED), U$112.1 (RED), U$144.1 (RED), U$176.1 (RED), U$208.1 (RED), U$240.1 (RED), U$272.1 (RED), U$304.1 (RED), U$336.1 (RED), U$368.1 (RED), U$400.1 (RED), U$432.1 (RED), U$464.1 (RED), U$496.1 (RED)
unnamed: U$2.12 (OUT12), U$16.3 (GREEN), U$48.3 (GREEN), U$80.3 (GREEN), U$112.3 (GREEN), U$144.3 (GREEN), U$176.3 (GREEN), U$208.3 (GREEN), U$240.3 (GREEN), U$272.3 (GREEN), U$304.3 (GREEN), U$336.3 (GREEN), U$368.3 (GREEN), U$400.3 (GREEN), U$432.3 (GREEN), U$464.3 (GREEN), U$496.3 (GREEN)
unnamed: U$2.13 (OUT13), U$16.4 (BLUE), U$48.4 (BLUE), U$80.4 (BLUE), U$112.4 (BLUE), U$144.4 (BLUE), U$176.4 (BLUE), U$208.4 (BLUE), U$240.4 (BLUE), U$272.4 (BLUE), U$304.4 (BLUE), U$336.4 (BLUE), U$368.4 (BLUE), U$400.4 (BLUE), U$432.4 (BLUE), U$464.4 (BLUE), U$496.4 (BLUE)
unnamed: U$2.14 (OUT14), U$17.1 (RED), U$49.1 (RED), U$81.1 (RED), U$113.1 (RED), U$145.1 (RED), U$177.1 (RED), U$209.1 (RED), U$241.1 (RED), U$273.1 (RED), U$305.1 (RED), U$337.1 (RED), U$369.1 (RED), U$401.1 (RED), U$433.1 (RED), U$465.1 (RED), U$497.1 (RED)
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
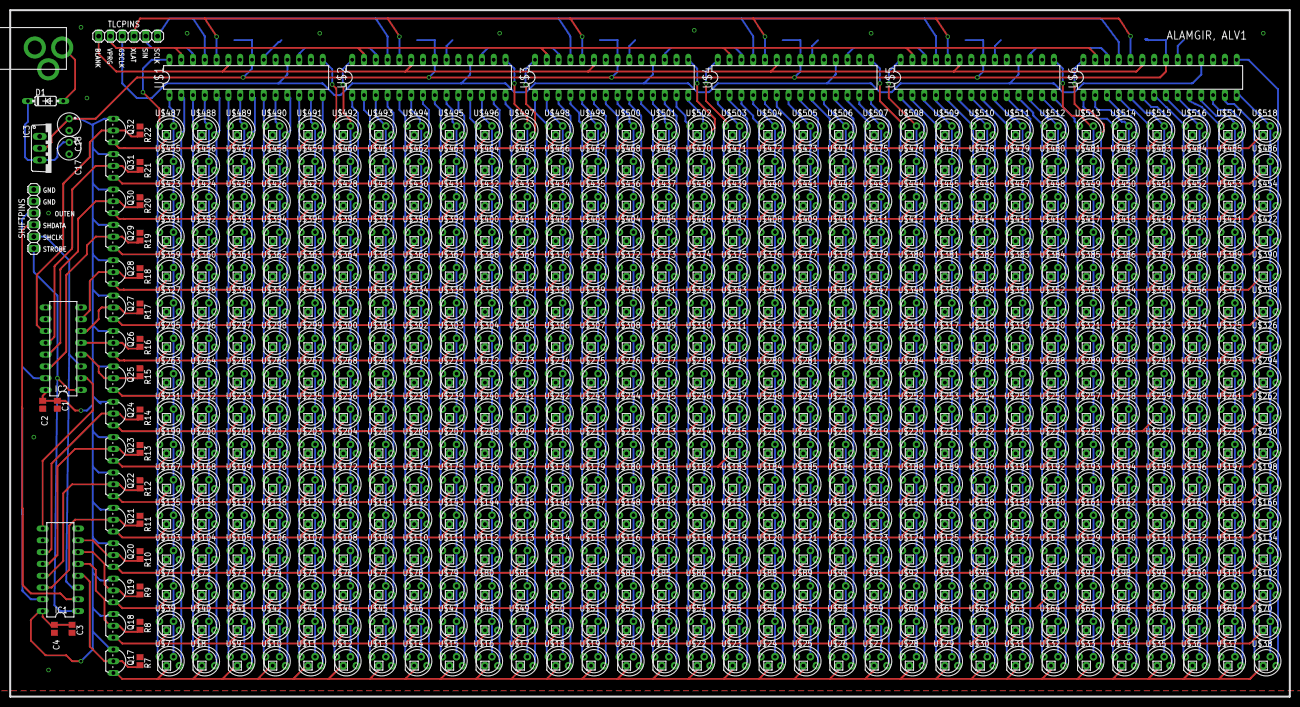
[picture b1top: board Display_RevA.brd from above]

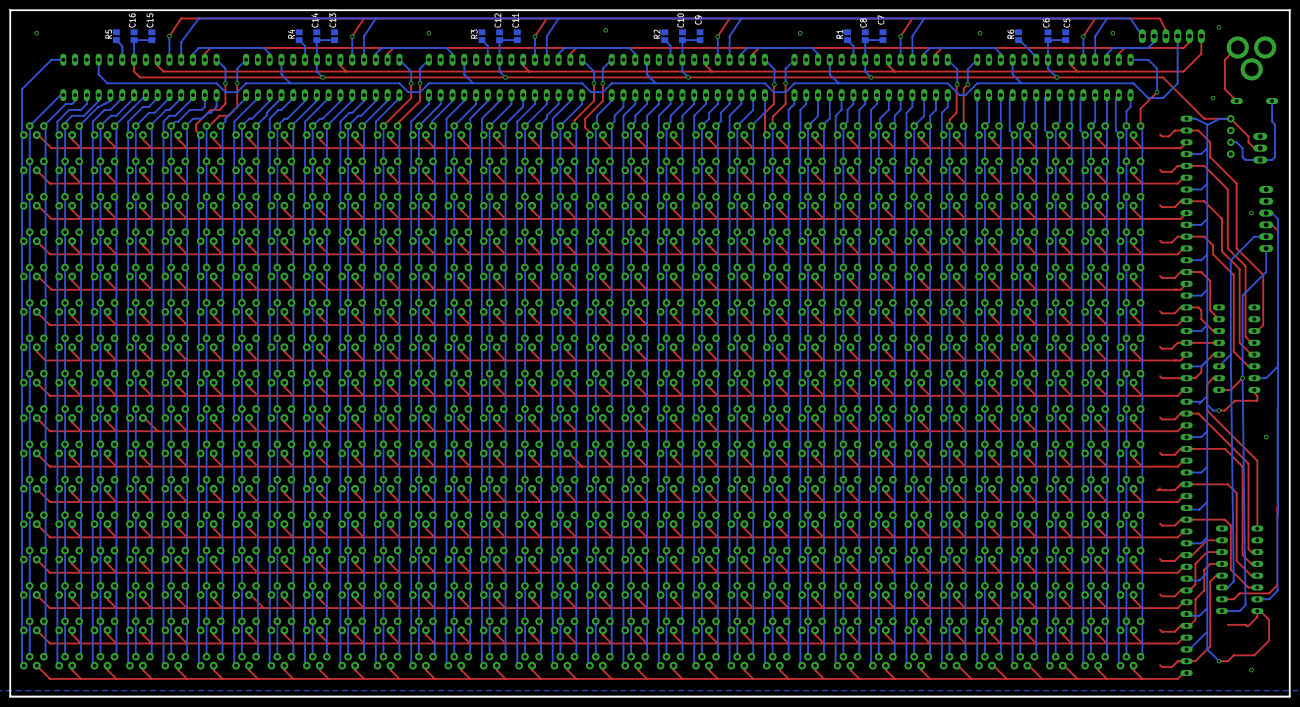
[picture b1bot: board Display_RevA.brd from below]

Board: 2 copper layers, 275.6 x 147.8 mm, 581 parts (18 on the bottom side), 154 nets.

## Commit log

2014-05-09 Fixed figures
